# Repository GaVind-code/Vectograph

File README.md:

# Vectograph

The Vectograph is an audio modifier in the sense that it controls what the audio volume is at; it tells you what is playing (Via Spotify) and can pause/play the audio output, and can fast forward and rewind on a track (Via Spotify) using the keys, and can display audio output via the 10 LEDs and the keys or the rotary encoder can also adjust audio. 

| Part                                | Qty |
| ----------------------------------- | --- |
| Seeed XIAO RP2040 microcontroller   | 1   |
| 1N4148 through-hole diodes          | 7   |
| MX-style mechanical switches        | 6   |
| EC11 rotary encoders (20mm D-shaft) | 1   |
| 0.91” 128×32 OLED display           | 1   |
| Blank DSA keycaps                   | 6   |
| SK6812 MINI-E RGB LEDs              | 10  |

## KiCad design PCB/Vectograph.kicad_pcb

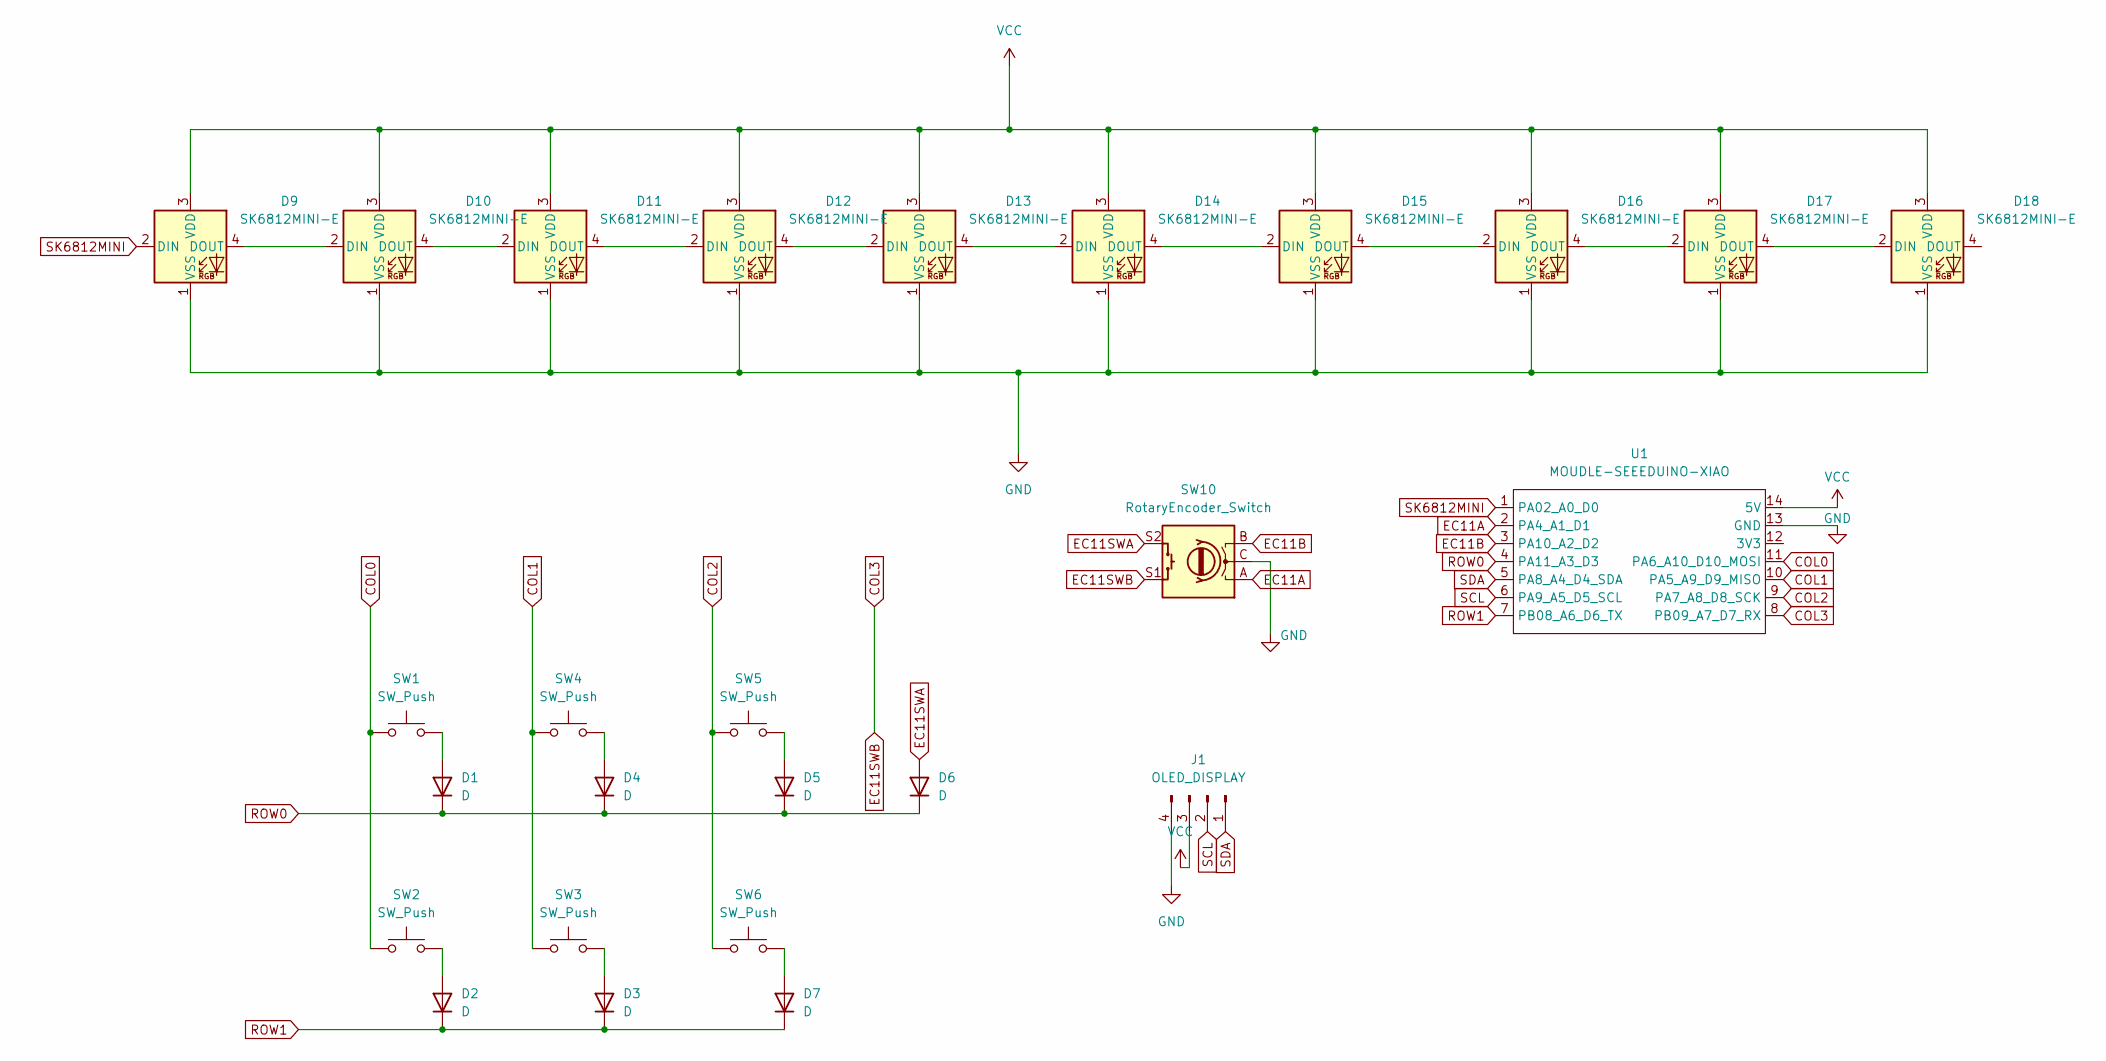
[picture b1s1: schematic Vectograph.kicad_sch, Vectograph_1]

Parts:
D1, D2, D3, D4, D5, D6, D7: D; D_DO-35_SOD27_P7.62mm_Horizontal
D9, D10, D11, D12, D13, D14, D15, D16, D17, D18: SK6812MINI-E; LED_SK6812MINI-E_3.2x2.8mm_P1.5mm_ReverseMount
J1: OLED_DISPLAY; SSD1306-0.91-OLED-4pin-128x32
SW1, SW2, SW3, SW4, SW5, SW6: SW_Push; SW_Cherry_MX_1.00u_PCB
SW10: RotaryEncoder_Switch; RotaryEncoder_Alps_EC11E-Switch_Vertical_H20mm
U1: MOUDLE-SEEEDUINO-XIAO; XIAO-Generic-Hybrid-14P-2.54-21X17.8MM

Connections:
COL0: SW1.1, SW2.1, U1.11 (PA6_A10_D10_MOSI)
COL1: SW3.1, SW4.1, U1.10 (PA5_A9_D9_MISO)
COL2: SW5.1, SW6.1, U1.9 (PA7_A8_D8_SCK)
COL3: SW10.S1, U1.8 (PB09_A7_D7_RX)
EC11A: SW10.A, U1.2 (PA4_A1_D1)
EC11B: SW10.B, U1.3 (PA10_A2_D2)
EC11SWA: D6.2 (A), SW10.S2
GND: D9.1 (VSS), D10.1 (VSS), D11.1 (VSS), D12.1 (VSS), D13.1 (VSS), D14.1 (VSS), D15.1 (VSS), D16.1 (VSS), D17.1 (VSS), D18.1 (VSS), J1.4, SW10.C, U1.13 (GND)
unnamed: D1.2 (A), SW1.2
unnamed: D2.2 (A), SW2.2
unnamed: D3.2 (A), SW3.2
unnamed: D4.2 (A), SW4.2
unnamed: D5.2 (A), SW5.2
unnamed: D7.2 (A), SW6.2
unnamed: D9.4 (DOUT), D10.2 (DIN)
unnamed: D10.4 (DOUT), D11.2 (DIN)
unnamed: D11.4 (DOUT), D12.2 (DIN)
unnamed: D12.4 (DOUT), D13.2 (DIN)
unnamed: D13.4 (DOUT), D14.2 (DIN)
unnamed: D14.4 (DOUT), D15.2 (DIN)
unnamed: D15.4 (DOUT), D16.2 (DIN)
unnamed: D16.4 (DOUT), D17.2 (DIN)
unnamed: D17.4 (DOUT), D18.2 (DIN)
ROW0: D1.1 (K), D4.1 (K), D5.1 (K), D6.1 (K), U1.4 (PA11_A3_D3)
ROW1: D2.1 (K), D3.1 (K), D7.1 (K), U1.7 (PB08_A6_D6_TX)
SCL: J1.2, U1.6 (PA9_A5_D5_SCL)
SDA: J1.1, U1.5 (PA8_A4_D4_SDA)
SK6812MINI: D9.2 (DIN), U1.1 (PA02_A0_D0)
VCC: D9.3 (VDD), D10.3 (VDD), D11.3 (VDD), D12.3 (VDD), D13.3 (VDD), D14.3 (VDD), D15.3 (VDD), D16.3 (VDD), D17.3 (VDD), D18.3 (VDD), J1.3, U1.14 (5V)

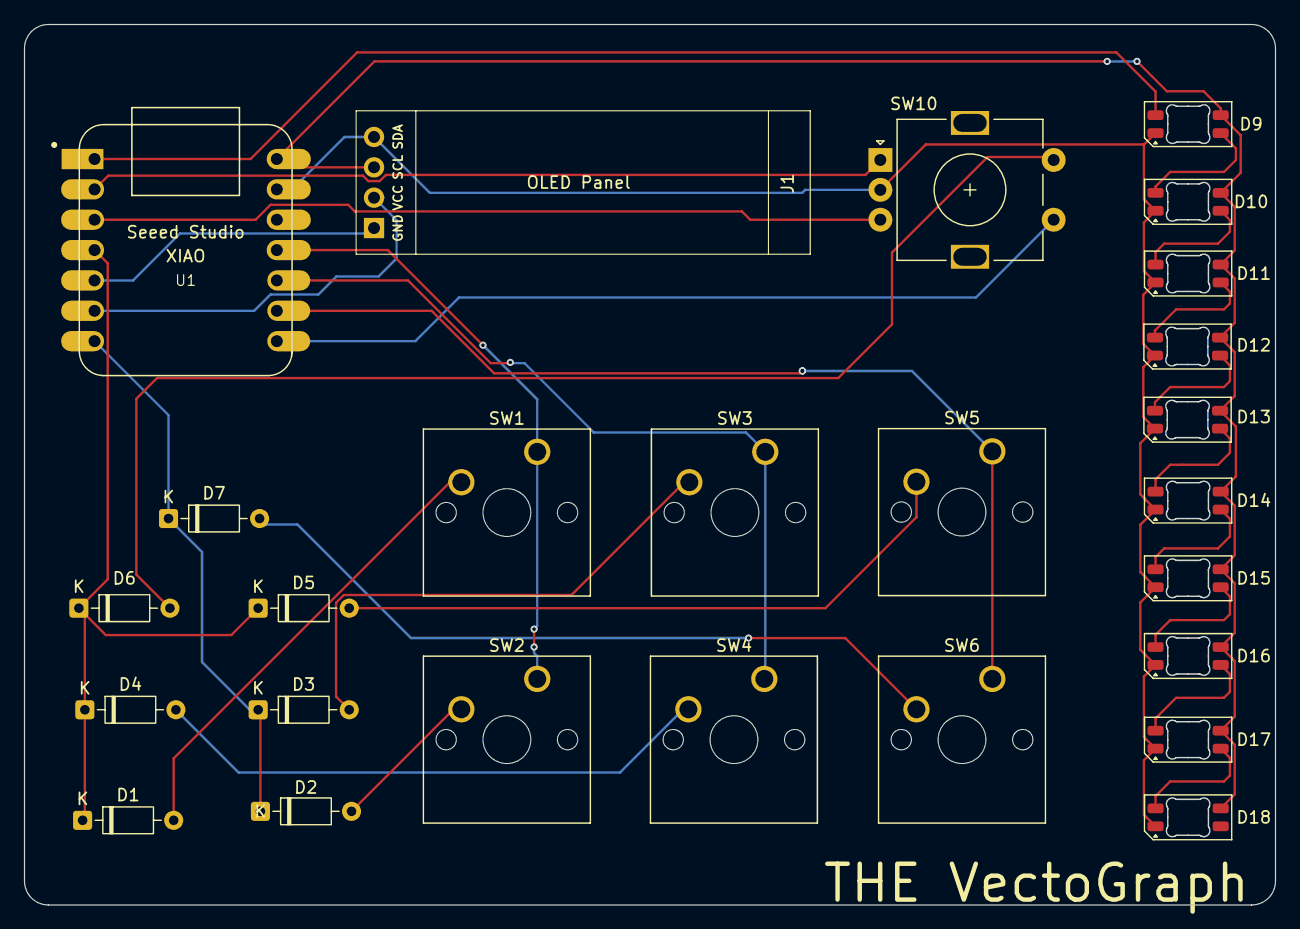
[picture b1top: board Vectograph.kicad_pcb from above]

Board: 2 copper layers, 104.7 x 73.7 mm, 26 parts (0 on the bottom side), 29 nets.

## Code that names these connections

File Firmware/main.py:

import board 

from kmk.kmk_keyboard import KMKKeyboard
from kmk.keys import KC
from kmk.scaners import DiodeOrientation
from kmk.extensions.media_keys import MediaKeys
from kmk.modules.encoder import EmcoderHandler
from kmk.extensions.RGB import RGB

emcoder_handler = EmcoderHandler()

keyboard = KMKKeyboard()
keyboard.extensions.append(MediaKeys())

keyboard.modules = [emcoder_handler]

COL0 = board.D10
COL1 = board.D9
COL2 = board.D8
COL3 = board.D7
ROW0 = board.D3
ROW1 = board.D6

col_pins = (COL0, COL1, COL2, COL3)
row_pins = (ROW0, ROW1)

keyboard.col_pins = col_pins
keyboard.row_pins = row_pins
keyboard.diode_orientation = DiodeOrientation.COL2ROW

keyboard.keymap = [
    [
        KC.MUTE, KC.VOLD, VOLU, KC.MUTE,
        KC.MRWD, KC.MPLY, KC.MFFD, KC.NO,
    ],
]

emcoder_handler.pins = (
    (board.D1, board.D2, None,),
)

emcoder_handler.map = [
    (
        (KC.VOLD, KC.VOLU, KC.NO),
    ),
]

rgb = RGB(pixel_pin=board.D0, num_pixels=10)
keybroad.extensions.append(rgb)

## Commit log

2026-06-17 Add temp.md
2026-06-17 Add temp.md file with initial content
2026-06-18 Enhance README with project details and images
    Added detailed description and images for the Vectograph project, including a parts list.
